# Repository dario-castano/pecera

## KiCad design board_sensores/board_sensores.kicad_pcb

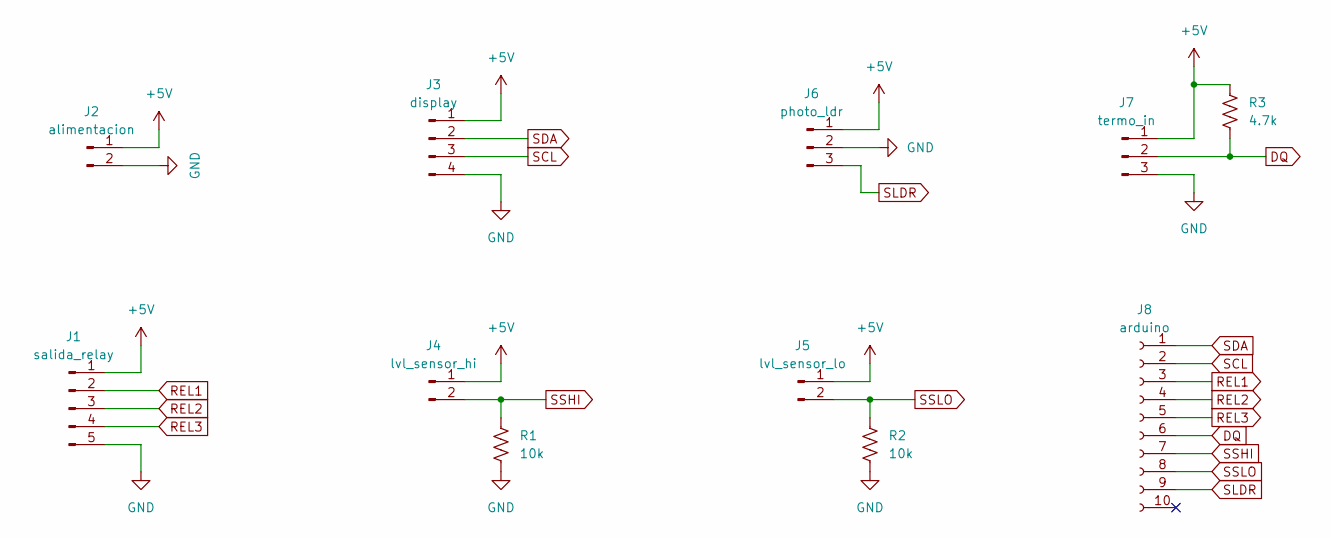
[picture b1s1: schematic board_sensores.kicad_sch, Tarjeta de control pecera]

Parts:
J1: salida_relay; PinHeader_1x05_P2.54mm_Vertical
J2: alimentacion; PinHeader_1x02_P2.54mm_Vertical
J3: display; PinHeader_1x04_P2.54mm_Vertical
J4: lvl_sensor_hi; PinHeader_1x02_P2.54mm_Vertical
J5: lvl_sensor_lo; PinHeader_1x02_P2.54mm_Vertical
J6: photo_ldr; PinHeader_1x03_P2.54mm_Vertical
J7: termo_in; PinHeader_1x03_P2.54mm_Vertical
J8: arduino; PinSocket_1x10_P2.54mm_Vertical
R1, R2: 10k; R_Axial_DIN0204_L3.6mm_D1.6mm_P5.08mm_Horizontal
R3: 4.7k; R_Axial_DIN0204_L3.6mm_D1.6mm_P5.08mm_Horizontal

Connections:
+5V: J1.1, J2.1, J3.1, J4.1, J5.1, J6.1, J7.1, R3.1
DQ: J7.2, J8.6, R3.2
GND: J1.5, J2.2, J3.4, J6.2, J7.3, R1.2, R2.2
REL1: J1.2, J8.3
REL2: J1.3, J8.4
REL3: J1.4, J8.5
SCL: J3.3, J8.2
SDA: J3.2, J8.1
SLDR: J6.3, J8.9
SSHI: J4.2, J8.7, R1.1
SSLO: J5.2, J8.8, R2.1

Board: 2 copper layers, 11 parts (0 on the bottom side), 11 nets, no tracks yet.

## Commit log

2022-05-30 Agrega constantes libreria display
2022-05-30 Agrega constructor y destructor pezlcd
2022-05-30 Implementa Pez_lcd library
2022-05-30 Modifica constructor pez_lcd
2022-05-30 Agrega prueba libreria pez_lcd
2022-06-01 Repara libreria PezLCD
2022-06-01 Elimina archivos innecesarios
2022-06-01 Agrega comentario a pezlcd
2022-06-03 Se configuran funciones para el display
2022-06-03 Agrega lectura LDR
2022-06-03 Ajusta lectura iluminacion
2022-06-03 Agrega dallas temperature
2022-06-03 Agrega parte inicial de registro de temperaturas
2022-06-04 Agrega lectura de temperatura en pantalla
2022-06-04 Agrega mensajes faltantes
2022-06-09 Agrega licencia GPL
